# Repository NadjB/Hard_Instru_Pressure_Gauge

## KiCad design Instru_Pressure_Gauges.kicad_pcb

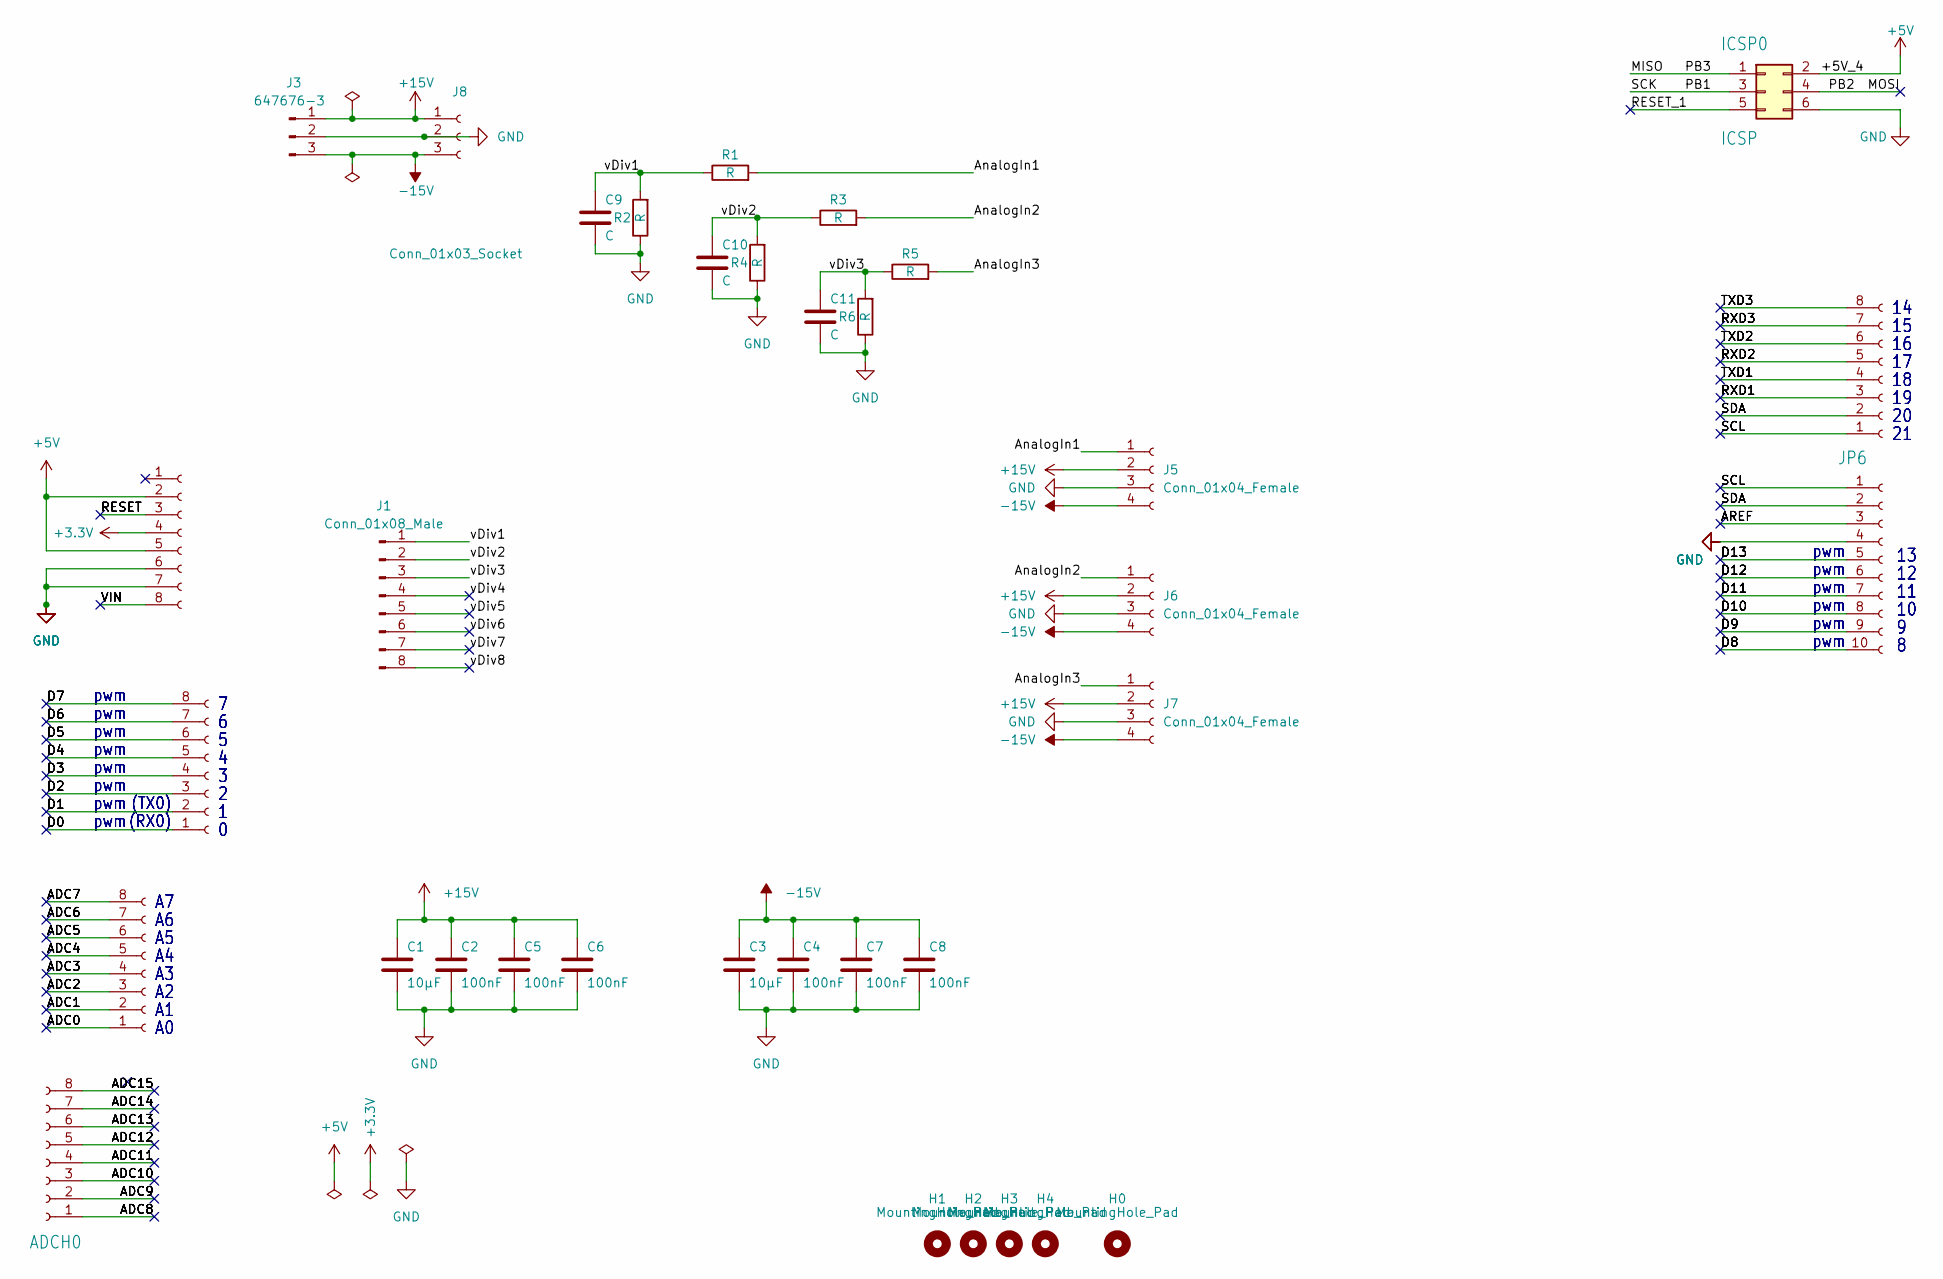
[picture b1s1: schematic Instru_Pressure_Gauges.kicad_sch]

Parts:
ADCH0: FH254-108DF08500V; PinHeader_1x08_P2.54mm_Vertical_Double
ADCL0: FH254-108DF08500V; PinHeader_1x08_P2.54mm_Vertical_Double
C1, C3: 10µF; C_1206_3216Metric_Pad1.33x1.80mm_HandSolder
C2, C4, C5, C6, C7, C8: 100nF; C_0603_1608Metric_Pad1.08x0.95mm_HandSolder
C9, C10, C11: C; C_0603_1608Metric_Pad1.08x0.95mm_HandSolder
COMMUNICATION0: FH254-108DF08500V; PinHeader_1x08_P2.54mm_Vertical_Double
H0, H1, H2, H3, H4: MountingHole_Pad; MountingHole_3.2mm_M3
ICSP0: ICSP; PinSocket_2x03_P2.54mm_Vertical
J1: Conn_01x08_Male; PinHeader_1x08_P2.54mm_Vertical
J3: 647676-3
J5, J6, J7: Conn_01x04_Female; TerminalBlock_TE_1-2834016-4_1x04_P2.54mm_Horizontal
J8: Conn_01x03_Socket; PinSocket_1x03_P2.54mm_Vertical
JP6: FH254-110DF08500V; PinHeader_1x10_P2.54mm_Vertical_Double
POWER0: FH254-108DF08500V; PinHeader_1x08_P2.54mm_Vertical_Double
PWML0: FH254-108DF08500V; PinHeader_1x08_P2.54mm_Vertical_Double
R1, R2, R3, R4, R5, R6: R; R_0805_2012Metric_Pad1.20x1.40mm_HandSolder

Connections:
+3.3V: POWER0.4
+5V: ICSP0.2, POWER0.2, POWER0.5
+15V: C1.1, C2.1, C5.1, C6.1, J3.1, J5.2, J6.2, J7.2, J8.1
-15V: C3.1, C4.1, C7.1, C8.1, J3.3, J5.4, J6.4, J7.4, J8.3
/ADC0: ADCL0.1
/ADC1: ADCL0.2
/ADC2: ADCL0.3
/ADC3: ADCL0.4
/ADC4: ADCL0.5
/ADC5: ADCL0.6
/ADC6: ADCL0.7
/ADC7: ADCL0.8
/ADC8: ADCH0.1
/ADC9: ADCH0.2
/ADC10: ADCH0.3
/ADC11: ADCH0.4
/ADC12: ADCH0.5
/ADC13: ADCH0.6
/ADC14: ADCH0.7
/ADC15: ADCH0.8
/AREF: JP6.3
/AnalogIn1: J5.1, R1.2
/AnalogIn2: J6.1, R3.2
/AnalogIn3: J7.1, R5.2
/D0: PWML0.1
/D1: PWML0.2
/D2: PWML0.3
/D3: PWML0.4
/D4: PWML0.5
/D5: PWML0.6
/D6: PWML0.7
/D7: PWML0.8
/D8: JP6.10
/D9: JP6.9
/D10: JP6.8
/D11: JP6.7
/D12: JP6.6
/D13: JP6.5
/MISO: ICSP0.1
/MOSI: ICSP0.4
/PB1: ICSP0.3
/RESET: POWER0.3
/RESET_1: ICSP0.5
/RXD1: COMMUNICATION0.3
/RXD2: COMMUNICATION0.5
/RXD3: COMMUNICATION0.7
/SCL: COMMUNICATION0.1, JP6.1
/SDA: COMMUNICATION0.2, JP6.2
/TXD1: COMMUNICATION0.4
/TXD2: COMMUNICATION0.6
/TXD3: COMMUNICATION0.8
/VIN: POWER0.8
/vDiv1: C9.1, J1.1, R1.1, R2.2
/vDiv2: C10.1, J1.2, R3.1, R4.2
/vDiv3: C11.1, J1.3, R5.1, R6.2
/vDiv4: J1.4
/vDiv5: J1.5
/vDiv6: J1.6
/vDiv7: J1.7
/vDiv8: J1.8
GND: C1.2, C2.2, C3.2, C4.2, C5.2, C6.2, C7.2, C8.2, C9.2, C10.2, C11.2, ICSP0.6, J3.2, J5.3, J6.3, J7.3, J8.2, JP6.4, POWER0.6, POWER0.7, R2.1, R4.1, R6.1

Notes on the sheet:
pwm
(TX0)
(RX0)

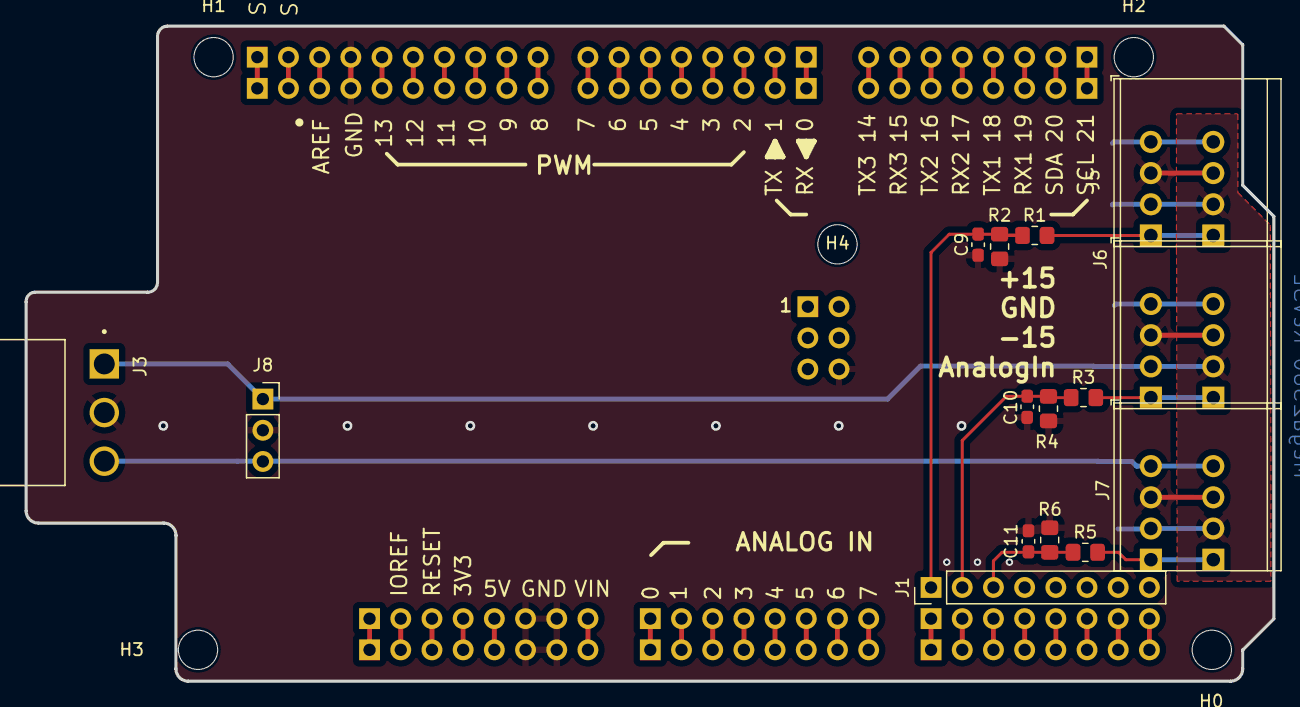
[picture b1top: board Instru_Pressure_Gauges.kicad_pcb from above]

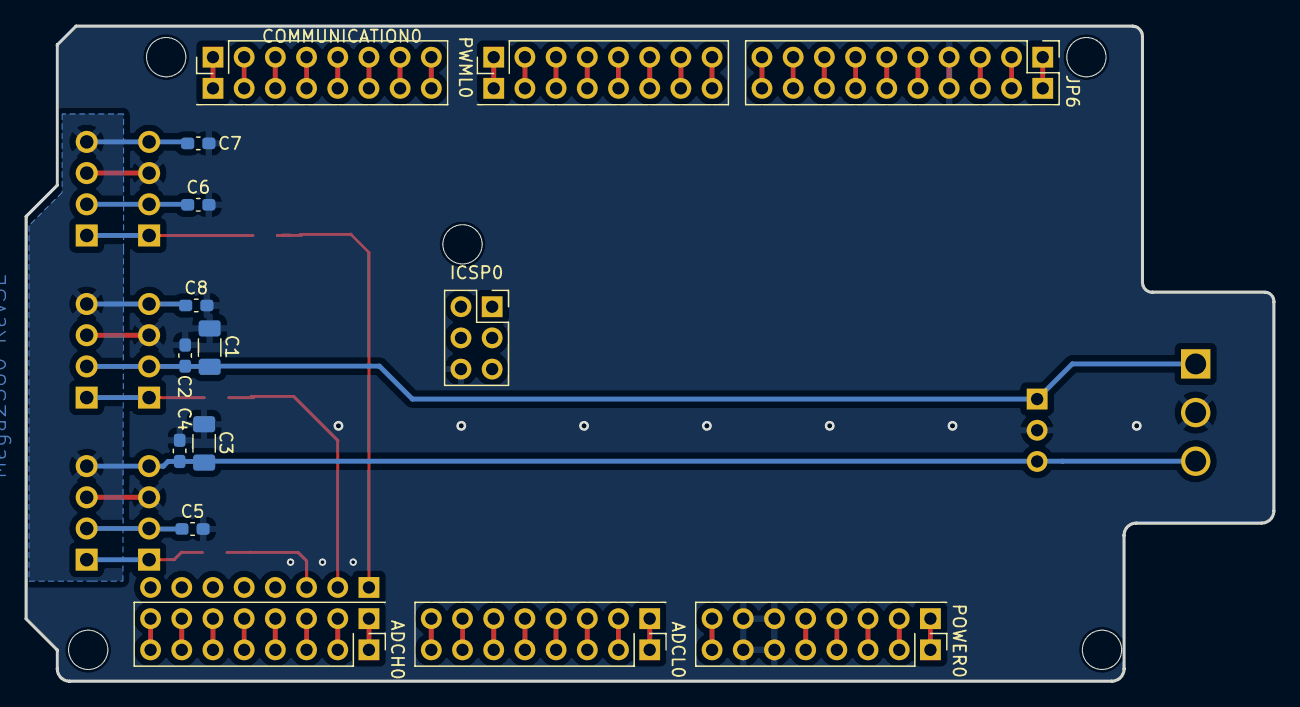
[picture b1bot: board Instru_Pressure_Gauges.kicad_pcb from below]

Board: 2 copper layers, 101.6 x 53.3 mm, 35 parts (15 on the bottom side), 12 nets.

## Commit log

2023-07-24 Synchronized MFC & Pressure gauge positions Changed transversal power connector
2023-07-26 Corrected routing non connection
2023-09-20 Update 10u for tantal
2023-12-01 Fabricated 10/10/23
